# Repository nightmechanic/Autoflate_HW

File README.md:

ADR1399E Voltage referebce circuit

mostly based on:
https://www.eevblog.com/forum/metrology/lm399-based-10-v-reference/

(specifically replies starting from 1300  to about 1343)

Designed in KiCad

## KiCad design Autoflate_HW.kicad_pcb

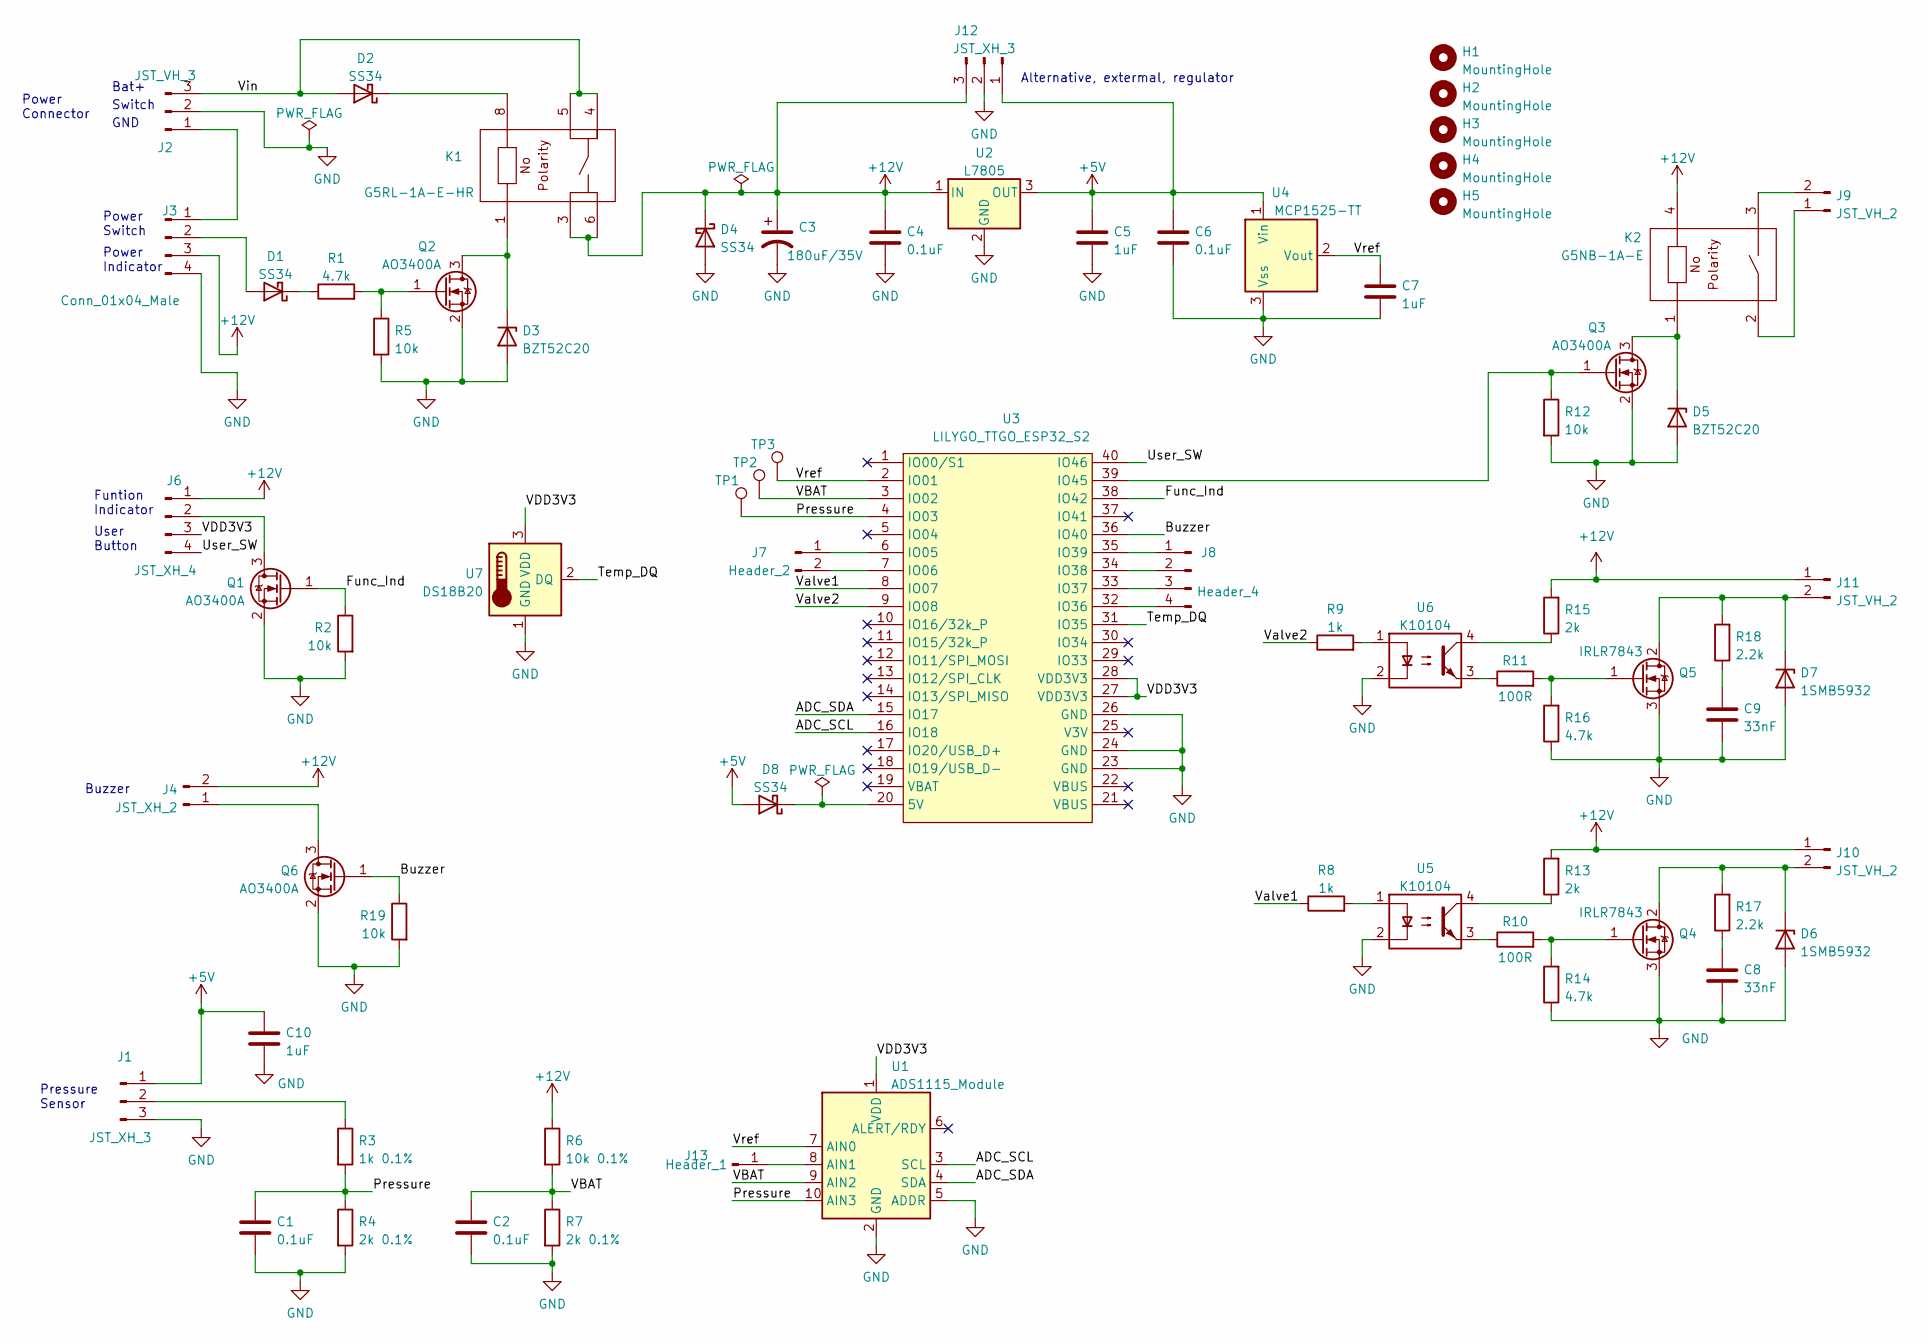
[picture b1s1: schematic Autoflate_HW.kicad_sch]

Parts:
C1, C2, C4, C6: 0.1uF; C_0805_2012Metric_Pad1.18x1.45mm_HandSolder
C3: 180uF/35V; CP_Radial_D12.5mm_P5.00mm
C5, C7, C10: 1uF; C_1206_3216Metric_Pad1.33x1.80mm_HandSolder
C8, C9: 33nF; C_0805_2012Metric_Pad1.18x1.45mm_HandSolder
D1, D2, D4, D8: SS34; D_SMA
D3, D5: BZT52C20; D_SOD-123
D6, D7: 1SMB5932; D_SMB
H1, H2, H3, H4, H5: MountingHole; MountingHole_3.2mm_M3
J1, J12: JST_XH_3; JST_XH_B3B-XH-A_1x03_P2.50mm_Vertical
J2: JST_VH_3; JST_VH_B3P-VH_1x03_P3.96mm_Vertical
J3: Conn_01x04_Male; JST_XH_B4B-XH-A_1x04_P2.50mm_Vertical
J4: JST_XH_2; JST_XH_B2B-XH-A_1x02_P2.50mm_Vertical
J6: JST_XH_4; JST_XH_B4B-XH-A_1x04_P2.50mm_Vertical
J7: Header_2; PinHeader_1x02_P2.54mm_Vertical
J8: Header_4; PinHeader_1x04_P2.54mm_Vertical
J9, J10, J11: JST_VH_2; JST_VH_B2P-VH_1x02_P3.96mm_Vertical
J13: Header_1; PinHeader_1x01_P2.54mm_Vertical
K1: G5RL-1A-E-HR; OMRON_G5RL_1A_E
K2: G5NB-1A-E; OMRON_G5NB_1A
Q1, Q2, Q3, Q6: AO3400A; SOT-23
Q4, Q5: IRLR7843; TO-252-2
R1, R14, R16: 4.7k; R_0805_2012Metric_Pad1.20x1.40mm_HandSolder
R2, R5, R12, R19: 10k; R_0805_2012Metric_Pad1.20x1.40mm_HandSolder
R3: 1k 0.1%; R_0805_2012Metric_Pad1.20x1.40mm_HandSolder
R4, R7: 2k 0.1%; R_0805_2012Metric_Pad1.20x1.40mm_HandSolder
R6: 10k 0.1%; R_0805_2012Metric_Pad1.20x1.40mm_HandSolder
R8, R9: 1k; R_0805_2012Metric_Pad1.20x1.40mm_HandSolder
R10, R11: 100R; R_0805_2012Metric_Pad1.20x1.40mm_HandSolder
R13, R15: 2k; R_0805_2012Metric_Pad1.20x1.40mm_HandSolder
R17, R18: 2.2k; R_0805_2012Metric_Pad1.20x1.40mm_HandSolder
TP1, TP2, TP3: TestPoint; TestPoint_Pad_D1.5mm
U1: ADS1115_Module; GY-ADS1115
U2: L7805; ST_D2PAK
U3: LILYGO_TTGO_ESP32_S2
U4: MCP1525-TT; SOT-23
U5, U6: K10104; K10104X
U7: DS18B20; TO-92_Inline

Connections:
+5V: C5.1, C6.1, C10.1, D8.2 (A), J1.1, J12.1, U2.3 (OUT), U4.1 (Vin)
+12V: C3.1, C4.1, D4.1 (K), J3.3, J4.2, J6.1, J10.1, J11.1, J12.3, K1.3, K1.6, K2.4, R6.1, R13.2, R15.2, U2.1 (IN)
/ADC_SCL: U1.3 (SCL), U3.16 (IO18)
/ADC_SDA: U1.4 (SDA), U3.15 (IO17)
/Buzzer: Q6.1 (G), R19.1, U3.36 (IO40)
/Func_Ind: Q1.1 (G), R2.1, U3.38 (IO42)
/Pressure: C1.1, R3.2, R4.1, TP1.1, U1.10 (AIN3), U3.4 (IO03)
/Temp_DQ: U3.31 (IO35), U7.2 (DQ)
/User_SW: J6.4, U3.40 (IO46)
/VBAT: C2.1, R6.2, R7.1, TP2.1, U1.9 (AIN2), U3.3 (IO02)
/VDD3V3: J6.3, U1.1 (VDD), U3.27 (VDD3V3), U3.28 (VDD3V3), U7.3 (VDD)
/Valve1: R8.1, U3.8 (IO07)
/Valve2: R9.1, U3.9 (IO08)
/Vin: D2.2 (A), J2.3, K1.4, K1.5
/Vref: C7.1, TP3.1, U1.7 (AIN0), U3.2 (IO01), U4.2 (Vout)
GND: C1.2, C2.2, C3.2, C4.2, C5.2, C6.2, C7.2, C8.2, C9.2, C10.2, D3.2 (A), D4.2 (A), D5.2 (A), D6.2 (A), D7.2 (A), J1.3, J2.2, J3.4, J12.2, Q1.2 (S), Q2.2 (S), Q3.2 (S), Q4.3 (S), Q5.3 (S), Q6.2 (S), R2.2, R4.2, R5.2, R7.2, R12.2, R14.1, R16.1, R19.2, U1.2 (GND), U1.5 (ADDR), U2.2 (GND), U3.23 (GND), U3.24 (GND), U3.26 (GND), U4.3 (Vss), U5.2, U6.2, U7.1 (GND)
unnamed: C8.1, R17.1
unnamed: C9.1, R18.1
unnamed: D1.1 (K), R1.1
unnamed: D1.2 (A), J3.2
unnamed: D2.1 (K), K1.8
unnamed: D3.1 (K), K1.1, Q2.3 (D)
unnamed: D5.1 (K), K2.1, Q3.3 (D)
unnamed: D6.1 (K), J10.2, Q4.2 (D), R17.2
unnamed: D7.1 (K), J11.2, Q5.2 (D), R18.2
unnamed: D8.1 (K), U3.20 (5V)
unnamed: J1.2, R3.1
unnamed: J2.1, J3.1
unnamed: J4.1, Q6.3 (D)
unnamed: J6.2, Q1.3 (D)
unnamed: J7.1, U3.6 (IO05)
unnamed: J7.2, U3.7 (IO06)
unnamed: J8.1, U3.35 (IO39)
unnamed: J8.2, U3.34 (IO38)
unnamed: J8.3, U3.33 (IO37)
unnamed: J8.4, U3.32 (IO36)
unnamed: J9.1, K2.2
unnamed: J9.2, K2.3
unnamed: J13.1, U1.8 (AIN1)
unnamed: Q2.1 (G), R1.2, R5.1
unnamed: Q3.1 (G), R12.1, U3.39 (IO45)
unnamed: Q4.1 (G), R10.2, R14.2
unnamed: Q5.1 (G), R11.2, R16.2
unnamed: R8.2, U5.1
unnamed: R9.2, U6.1
unnamed: R10.1, U5.3
unnamed: R11.1, U6.3
unnamed: R13.1, U5.4
unnamed: R15.1, U6.4

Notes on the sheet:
GND
Power Switch
Switch
Power Connector
Buzzer
Power Indicator
Bat+
Funtion Indicator
Alternative, extermal, regulator
User Button
Pressure Sensor

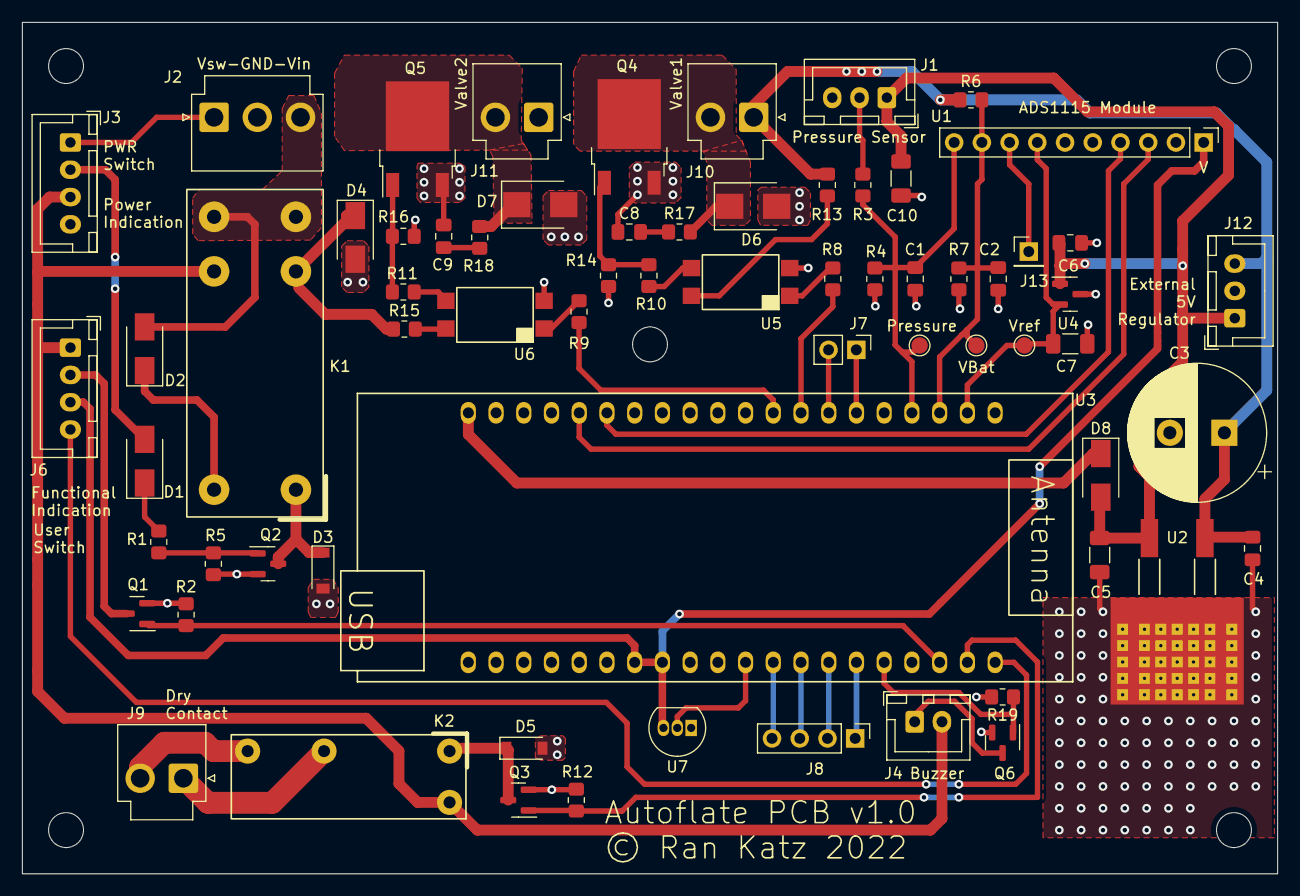
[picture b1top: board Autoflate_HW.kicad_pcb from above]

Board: 2 copper layers, 115.0 x 78.0 mm, 72 parts (0 on the bottom side), 49 nets.

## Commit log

2022-09-11 Added Cap on pressure sensor supply
2022-09-13 4 pin xh
2022-09-14 Added TTGO board 3d model
2022-09-15 Generated schematic pdf
2022-11-03 added buzzer connection
2022-11-03 Updated revision, added revision description

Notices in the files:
Autoflate_HW.kicad_pcb:
© Ran Katz 2022
